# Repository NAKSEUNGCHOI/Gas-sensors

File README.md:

# Project Gas(Air quality) sensors

* University of Washington Summer 2022 
* Prof. Vikram Iyer.
* Nakseung Choi | graduate research assistant @ SSOL UW 

## Description

* Prof. Vikram Iyer and I are currently building low power low cost gas sensors (CO2, CO, and black carbon) to help two groups of scientists collect data for their research studies. One group wants to get data in the greater Seattle area to study on where these gasses are coming from. Ultimately, they would like to expand the number of the gas sensors in different locations such that they can compare with other locations for further studies.
The other group would like to place these gas sensors in the middle of moutains in the eastern Washington to study how these gases(CO2 and CO) affect wild animals when there is an unexpected wildfire going. 

* We are currently testing several CO2 sensors to compare their functionality with a commercial device. In the mean time, we just got done with our own PCB design for SPEC CO sensor as well as hardware/software integration. Depending on how precise data the scientists need, we are going to make it acordingly. nRF52480 Arm Cortex-m4 is probably going to be used for the MCU. Using Lora radio communication, a long distance communication interface will also be implemented to update data to the web server such that the scientists can check the data in real time.  

## Authors

- Nakseung Choi
- Please check out my Linkedin: https://www.linkedin.com/in/nakseung-choi-090a1b69/

## Release Notes

* <pre> New Tube arrived. About to go install the MA350 on the rooftop                       11-22-2022</pre>
* <pre> 300ml/min 60 ml/min for 5 wavelengths tests are done. missing 60 ml/min with UV+IR    9-12-2022</pre>
* <pre> Created another python code to draw different plots for CO2 sensors                   9-12-2022</pre>
* <pre> Wrote a python code to plot CO2 sensors - avg of two aranets for 4 sensors            9-08-2022</pre>
* <pre> wrote a python program using mathplot to graph the CO2 data  (Still testing MA350)    9-07-2022</pre>
* <pre> Testing the MA350                                                                     8-29-2022</pre>
* <pre> arduino / python serial communication script complete. Sending data to adafruitIO     8-26-2022</pre>
* <pre> presentation done. more CO testing / preparing to set up MA350.                       8-24-2022</pre>                                                
* <pre> got the CO sensor working with noise. more testing...........                         8-23-2022</pre>
* <pre> created a new PCB board and testing..                                                 8-22-2022</pre>
* <pre> presentation preparation2                                                             8-20-2022</pre>
* <pre> presentation preparation                                                              8-20-2022</pre>
* <pre> Software done. software/hardware integration started                                  8-18-2022</pre>
* <pre> Testing CO sensor 2                                                                   8-17-2022</pre>
* <pre> Testing CO sensor                                                                     8-16-2022</pre>
* <pre> setting up Black Carbon sensor & CO sensor                                            8-15-2022</pre>
* <pre> testing two SCD41s, two aranets, two PASCO2s all together.                            8-15-2022</pre>
* <pre>Debugging Complete. Ready to go for a testing.                                         8-14-2022</pre>
* <pre>Debugging...                                                                           8-12-2022</pre>
* <pre>PASCO2s are going to be tested with scd41 and aranet4 together for the functionality   8-11-2022</pre>
* <pre>Xensiv PAS CO2 coding in python complete.                                              8-11-2022</pre>
* <pre>Xensiv PAS CO2 working. Testing started.                                               8-10-2022</pre>
* <pre>Debugging Xensiv PAS CO2                                                               8-09-2022</pre>
* <pre>Testing Xensiv PAS CO2 manufactured by Infineon.                                       8-08-2022</pre>
* <pre>All parts are done soldering onto the board. Going to test the PCB.                    8-07-2022</pre>
* <pre>CO sensor PCB design complete. About to sorder the CO sensor circuit.                  8-03-2022</pre> 
* <pre>Designing a new circuit for CO sensor due to the chip shortage (LMP9100 out of stock)  8-02-2022</pre>
* <pre>Installed CO2 sensor's in an office with two people.                                   7-28-2022</pre>
* <pre>CO Sensor PCB Design V2 complete.                                                      7-28-2022</pre>
* <pre>CO Sensor PCB Design complete.                                                         7-27-2022</pre>
* <pre>Testing 24 hours success.                                                              7-26-2022</pre>
* <pre>Testing two SCD41s and two aranets4s on Raspberry pi 3.                                7-25-2022</pre>
* <pre>Working on PCB design for CO sensor                                                    7-24-2022</pre>
* <pre>Implemented two SCD41s and two aranet4s on Raspberry pi 3 for a testing.               7-21-2022</pre>
* <pre>Implemented SCD41 on nRF52480 express with Lora Radio (RFM9x)                          7-07-2022</pre>
* <pre>Implemented SCD41 (via I2C) and Aranet4 (via Bluetooth) on Raspberry pi 3 (B type)     7-01-2022</pre>
* <pre>Started                                                                                6/24/2022</pre>

## License

Copyright @ Nakseung Choi.

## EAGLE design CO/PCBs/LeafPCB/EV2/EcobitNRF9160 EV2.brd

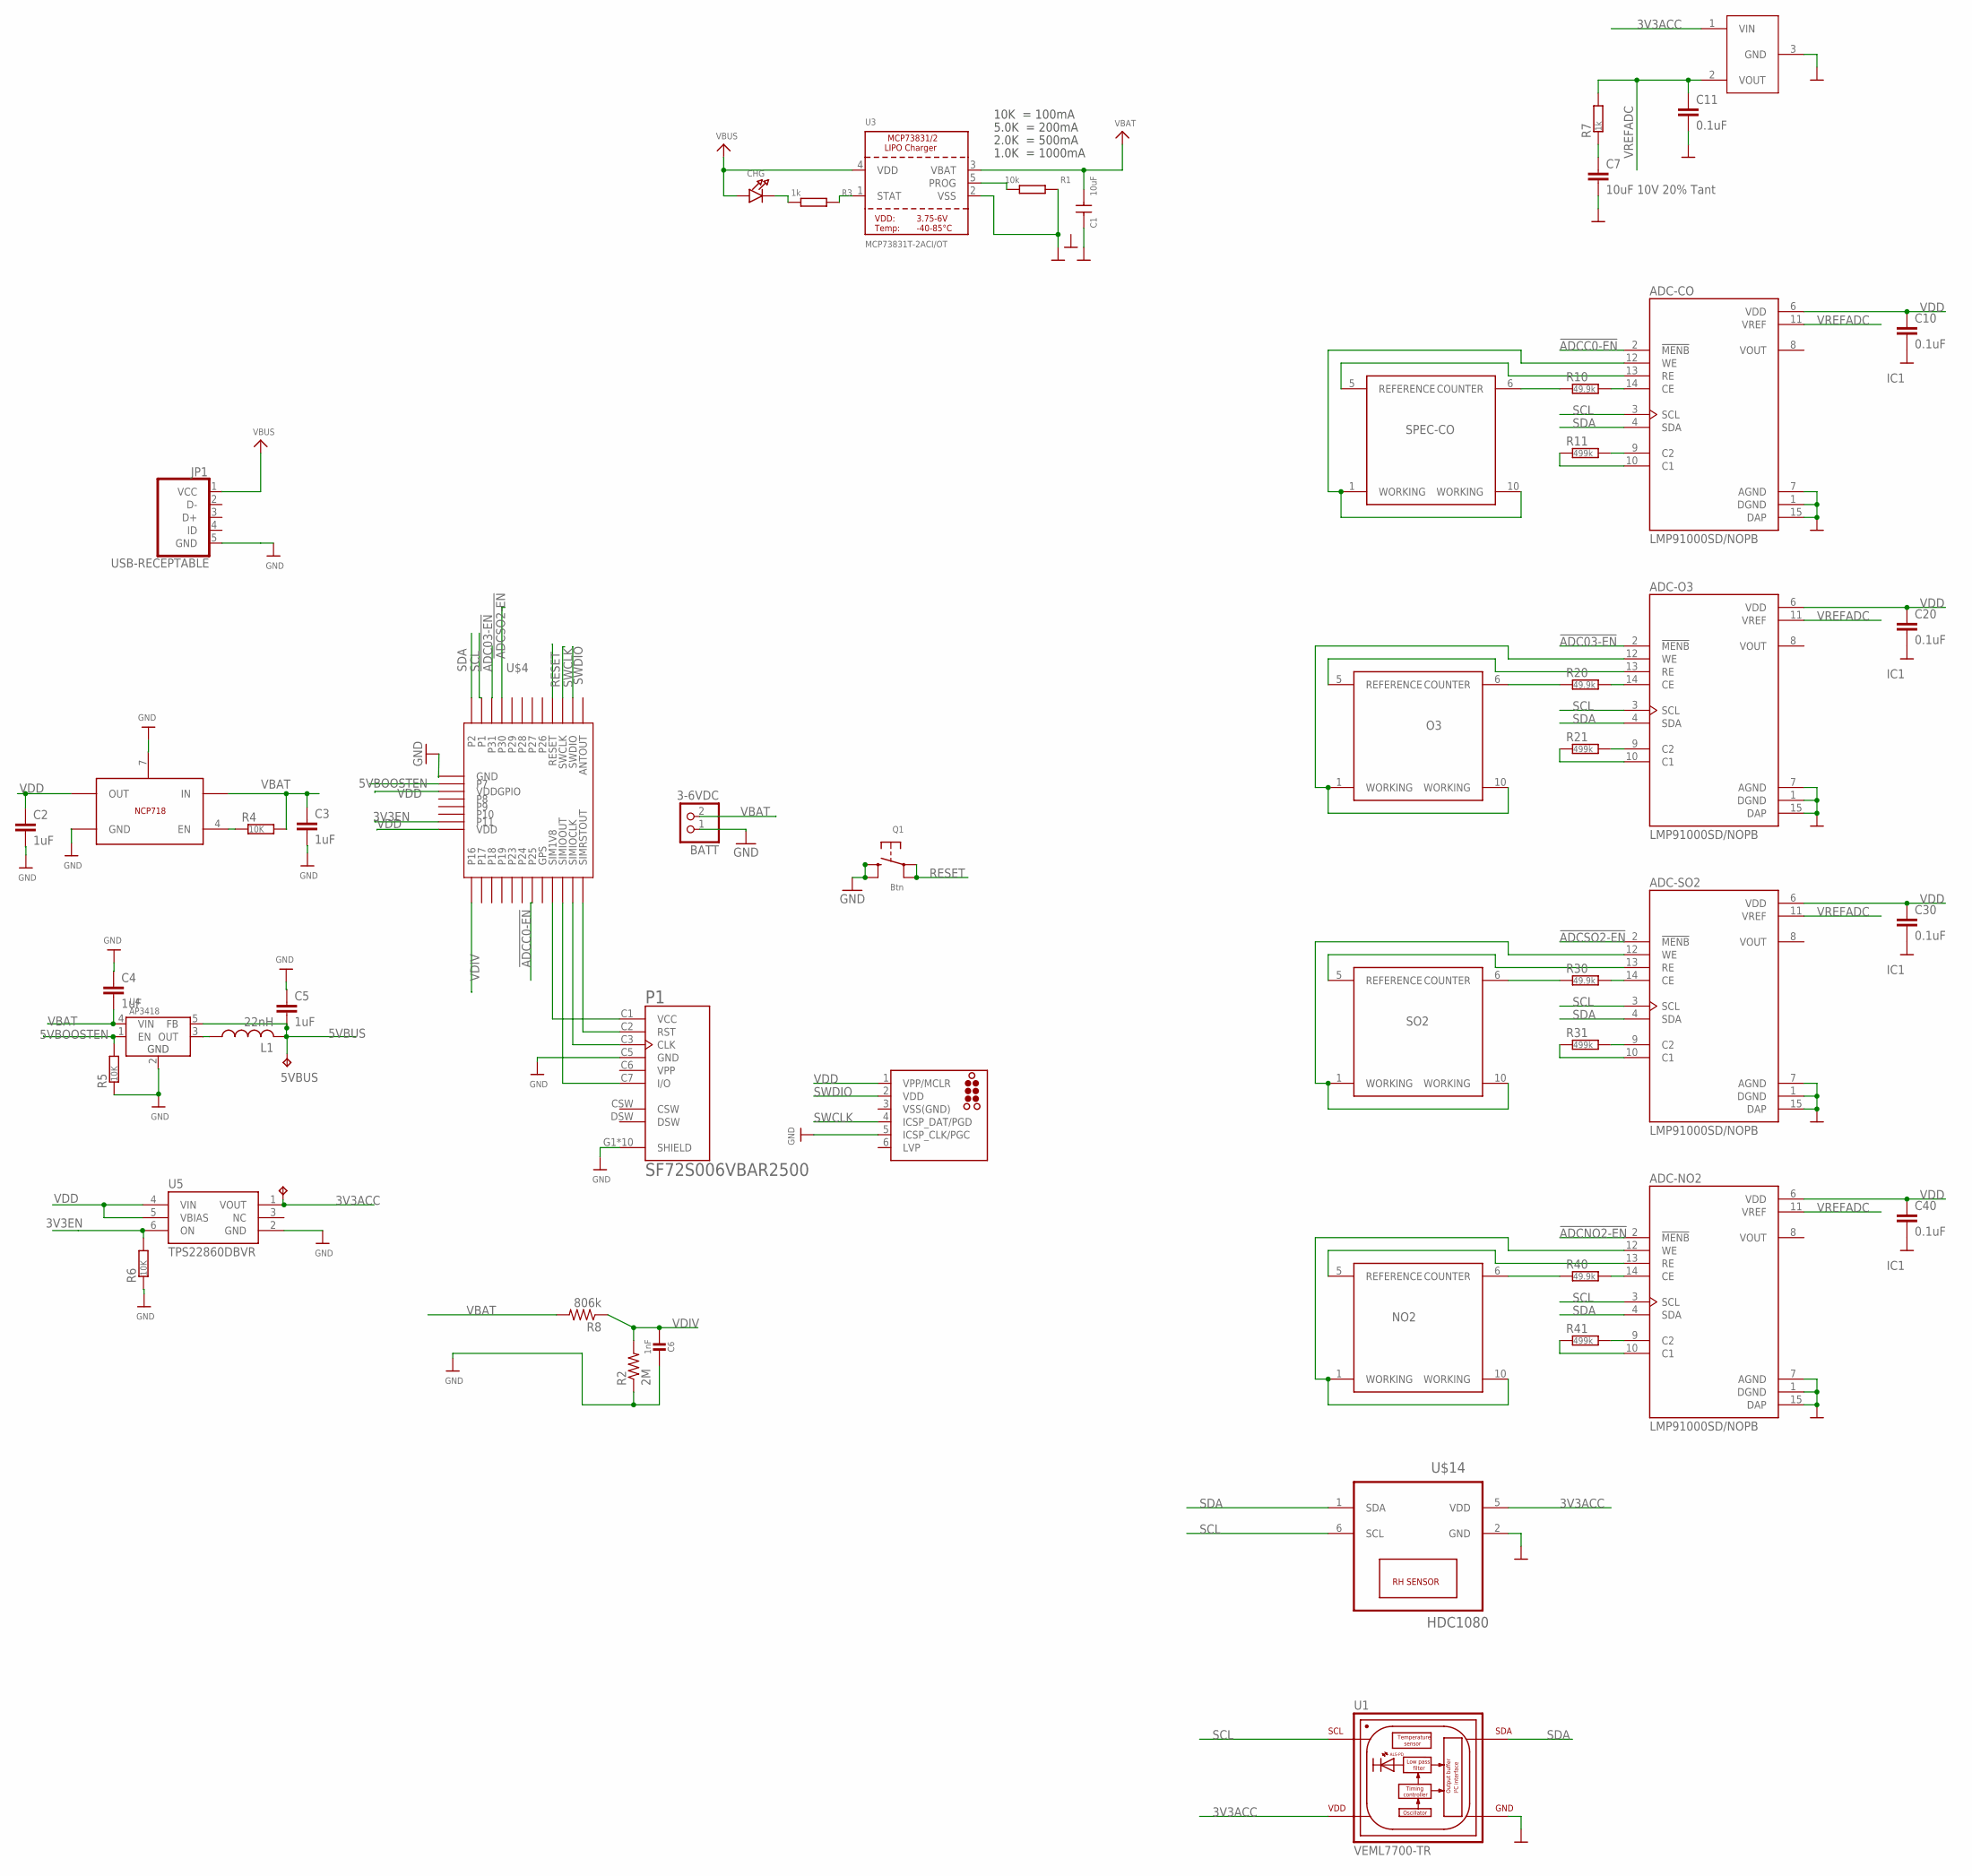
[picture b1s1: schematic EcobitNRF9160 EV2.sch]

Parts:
5VBUS, 5VBUS1: TPTP15R; TP15R
ADC-CO: LMP91000SD/NOPB; SON50P400X400X80-15N
ADC-NO2: LMP91000SD/NOPB; SON50P400X400X80-15N
ADC-O3: LMP91000SD/NOPB; SON50P400X400X80-15N
ADC-SO2: LMP91000SD/NOPB; SON50P400X400X80-15N
BATT: 3-6VDC; JSTPH2
C1: 10uF; C-0402
C2, C3, C4, C5: 1uF; RESC0402_N
C6: 1nF; 0603-NO
C7: 10uF 10V 20% Tant; RESC0805_N
C10, C11, C20, C30, C40: 0.1uF; RESC0603_N
CHG: LED0805_NOOUTLINE; CHIPLED_0805_NOOUTLINE
IC1: ISL60002DIH320Z-TK; SOT-23-3
J2: TC2030-MCP-NL
JP1: USB-RECEPTABLE; FCI-10103594-0001LF
L1: 22nH; RESC0603_N
NO2: SPECSENSOR
O3: SPECSENSOR
P1: SF72S006VBAR2500; JAE_SF72S006VBAR2500
Q1: Btn; BTN_KMR2_4.6X2.8
R1: 10k; R0402
R2: 2M; R0603
R3: 1k; R0402
R4, R5, R6: 10K; RESC0402_N
R7: 1k; RESC0603_N
R8: 806k; R0603
R10, R20, R30, R40: 49.9k; RESC0603_N
R11, R21, R31, R41: 499k; RESC0603_N
SO2: SPECSENSOR
SPEC-CO: SPECSENSOR
U1: VEML7700-TR; XDCR_VEML7700-TR
U2: NCP718; NCP718-WDFN6
U3: MCP73831T-2ACI/OT; SOT23-5
U4: AP3418; SOT25
U5: TPS22860DBVR; R-PDSO-G6
U$4: NRF9160MODULE
U$14: HDC1080; TI-S-PWSON-N6

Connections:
3V3ACC: 5VBUS1.TP, IC1.1 (VIN), U1.2 (VDD), U5.1 (VOUT), U$14.5 (VDD)
3V3EN: R6.2, U5.6 (ON), U$4.P11
5VBOOSTEN: R5.2, U4.1 (EN), U$4.P7
5VBUS: 5VBUS.TP, C5.2, L1.2, U4.5 (FB)
!ADC03-EN: ADC-O3.2 (!MENB), U$4.P31
!ADCC0-EN: ADC-CO.2 (!MENB), U$4.P25
!ADCNO2-EN: ADC-NO2.2 (!MENB)
!ADCSO2-EN: ADC-SO2.2 (!MENB), U$4.P30
GND: ADC-CO.1 (DGND), ADC-CO.7 (AGND), ADC-CO.15 (DAP), ADC-NO2.1 (DGND), ADC-NO2.7 (AGND), ADC-NO2.15 (DAP), ADC-O3.1 (DGND), ADC-O3.7 (AGND), ADC-O3.15 (DAP), ADC-SO2.1 (DGND), ADC-SO2.7 (AGND), ADC-SO2.15 (DAP), BATT.1, C1.2, C2.2, C3.2, C4.1, C5.1, C6.1, C7.2, C10.2, C11.2, C20.2, C30.2, C40.2, IC1.3 (GND), J2.5 (ICSP_CLK/PGC), JP1.5 (GND), P1.C5 (GND), P1.G1 (SHIELD), P1.G2 (SHIELD), P1.G3 (SHIELD), P1.G4 (SHIELD), P1.G5 (SHIELD), P1.G6 (SHIELD), P1.G7 (SHIELD), P1.G8 (SHIELD), P1.G9 (SHIELD), P1.G10 (SHIELD), Q1.B (S), Q1.B' (S1), R1.1, R2.1, R5.1, R6.1, U1.3 (GND), U2.3 (GND), U2.7 (GND), U3.2 (VSS), U4.2 (GND), U5.2 (GND), U$4.GND, U$14.2 (GND)
unnamed: P1.C1 (VCC), U$4.SIM1V8
unnamed: L1.1, U4.3 (OUT)
unnamed: R3.1, U3.1 (STAT)
unnamed: CHG.C, R3.2
unnamed: P1.C2 (RST), U$4.SIMRSTOUT
unnamed: P1.C3 (CLK), U$4.SIMCLKOUT (SIMIOCLK)
unnamed: P1.C7 (I/O), U$4.SIMIOOUT
unnamed: ADC-CO.9 (C2), R11.2
unnamed: ADC-CO.10 (C1), R11.1
unnamed: R1.2, U3.5 (PROG)
unnamed: ADC-CO.14 (CE), R10.2
unnamed: C7.1, R7.1
unnamed: ADC-O3.9 (C2), R21.2
unnamed: ADC-O3.10 (C1), R21.1
unnamed: ADC-O3.14 (CE), R20.2
unnamed: ADC-SO2.9 (C2), R31.2
unnamed: ADC-SO2.10 (C1), R31.1
unnamed: ADC-SO2.14 (CE), R30.2
unnamed: ADC-NO2.9 (C2), R41.2
unnamed: ADC-NO2.10 (C1), R41.1
unnamed: ADC-NO2.14 (CE), R40.2
R-EN: R4.1, U2.4 (EN)
RESET: Q1.A, Q1.A' (P1), U$4.RESET
SCL: ADC-CO.3 (SCL), ADC-NO2.3 (SCL), ADC-O3.3 (SCL), ADC-SO2.3 (SCL), U1.1 (SCL), U$4.P1, U$14.6 (SCL)
SDA: ADC-CO.4 (SDA), ADC-NO2.4 (SDA), ADC-O3.4 (SDA), ADC-SO2.4 (SDA), U1.4 (SDA), U$4.P2, U$14.1 (SDA)
SPEC-CO-COUNTER: R10.1, SPEC-CO.6 (COUNTER)
SPEC-CO-REF: ADC-CO.13 (RE), SPEC-CO.5 (REFERENCE)
SPEC-CO-WKG: ADC-CO.12 (WE), SPEC-CO.1 (WORKING), SPEC-CO.10 (WORKING)
SPEC-NO2-COUNTER: NO2.6 (COUNTER), R40.1
SPEC-NO2-REF: ADC-NO2.13 (RE), NO2.5 (REFERENCE)
SPEC-NO2-WKG: ADC-NO2.12 (WE), NO2.1 (WORKING), NO2.10 (WORKING)
SPEC-O3-COUNTER: O3.6 (COUNTER), R20.1
SPEC-O3-REF: ADC-O3.13 (RE), O3.5 (REFERENCE)
SPEC-O3-WKG: ADC-O3.12 (WE), O3.1 (WORKING), O3.10 (WORKING)
SPEC-SO2-COUNTER: R30.1, SO2.6 (COUNTER)
SPEC-SO2-REF: ADC-SO2.13 (RE), SO2.5 (REFERENCE)
SPEC-SO2-WKG: ADC-SO2.12 (WE), SO2.1 (WORKING), SO2.10 (WORKING)
SWCLK: J2.4 (ICSP_DAT/PGD), U$4.SWCLK
SWDIO: J2.2 (VDD), U$4.SWDIO
VBAT: BATT.2, C1.1, C3.1, C4.2, R4.2, R8.2, U2.6 (IN), U3.3 (VBAT), U4.4 (VIN)
VBUS: CHG.A, JP1.1 (VCC), U3.4 (VDD)
VDD: ADC-CO.6 (VDD), ADC-NO2.6 (VDD), ADC-O3.6 (VDD), ADC-SO2.6 (VDD), C2.1, C10.1, C20.1, C30.1, C40.1, J2.1 (VPP/MCLR), U2.1 (OUT), U5.4 (VIN), U5.5 (VBIAS), U$4.VDD, U$4.VDDGPIO
VDIV: C6.2, R2.2, R8.1, U$4.P16
VPP: P1.C6 (VPP)
VREFADC: ADC-CO.11 (VREF), ADC-NO2.11 (VREF), ADC-O3.11 (VREF), ADC-SO2.11 (VREF), C11.1, IC1.2 (VOUT), R7.2
VSS(GND): J2.3 (VSS(GND))

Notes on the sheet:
10K = 100mA
5.0K = 200mA
2.0K = 500mA
1.0K = 1000mA

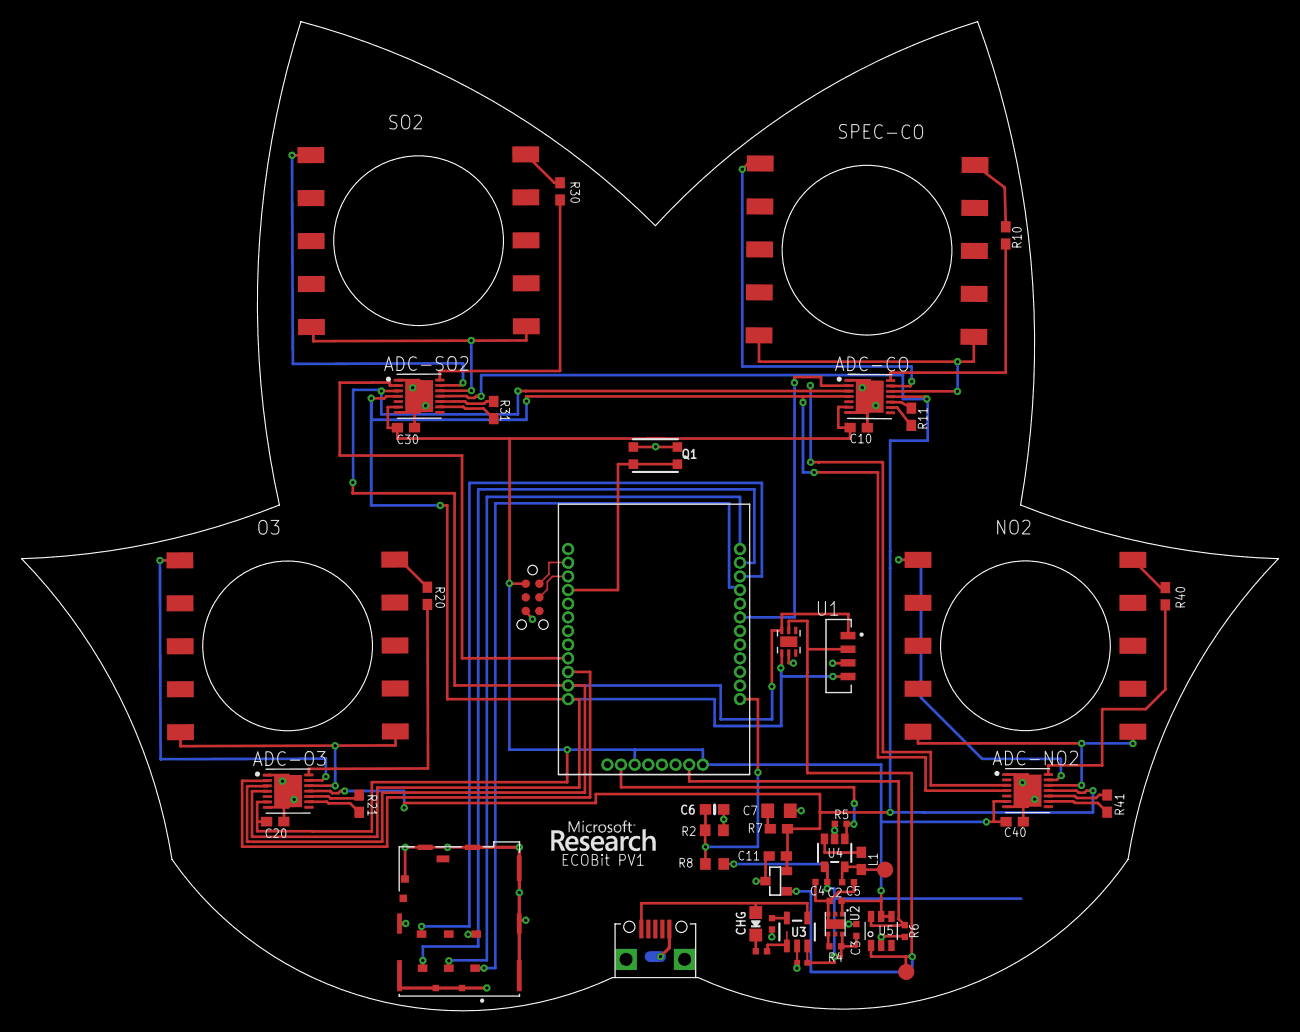
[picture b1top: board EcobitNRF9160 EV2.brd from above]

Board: 2 copper layers, 117.0 x 92.1 mm, 53 parts (1 on the bottom side), 52 nets.

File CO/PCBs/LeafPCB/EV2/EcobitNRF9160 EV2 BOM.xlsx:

Column1 | Column2 | Column3 | Column4
Part | Value | Device | Package
ADC-CO | LMP91000SD/NOPB | LMP91000SD/NOPB | SON50P400X400X80-15N
ADC-NO2 | LMP91000SD/NOPB | LMP91000SD/NOPB | SON50P400X400X80-15N
ADC-O3 | LMP91000SD/NOPB | LMP91000SD/NOPB | SON50P400X400X80-15N
ADC-SO2 | LMP91000SD/NOPB | LMP91000SD/NOPB | SON50P400X400X80-15N
BATT | 3-6VDC | CON_JST_PH_2PIN | JSTPH2
C1 | 10uF | CAP0402 | C-0402
C2, C3, C4, C5, C6 | 1uF | CAPACITOR_0402_N | RESC0402_N
C7 | 10uF 10V 20% Tant | CAPACITOR_0805_N | RESC0805_N
C10, C11, C20, C30, C40 | 0.1uF | CAPACITOR_0603_N | RESC0603_N
CHG |  | LED0805_NOOUTLINE | CHIPLED_0805_NOOUTLINE
IC1 | ISL60002DIH320Z-TK | ISL60002DIH320Z-TK | SOT-23-3
JP1 | USB-RECEPTABLE | USB-RECEPTABLE | FCI-10103594-0001LF
L1 | 22nH | INDUCTOR_0603_N | RESC0603_N
P1 | SF72S006VBAR2500 | SF72S006VBAR2500 | JAE_SF72S006VBAR2500
Q1 | Btn | SWITCH_TACT_SMT4.6X2.8 | BTN_KMR2_4.6X2.8
R1, R4, R5, R6 | 10k | RESR0402 | R0402
R2 | 2M | R-US_R0603 | R0603
R3, R7 | 1k | RESR0402 | R0402
R11, R21, R31, R41 | 499k | RESISTOR_0603_N | RESC0603_N
R8 | 806k | R-US_R0603 | R0603
R10, R20, R30, R40 | 49.9k | RESISTOR_0603_N | RESC0603_N
IC2 | HDC1080 | HDC1080 | TI-S-PWSON-N6
U1 | VEML7700-TR | VEML7700-TR | XDCR_VEML7700-TR
U2 | NCP718 | NCP718 | NCP718-WDFN6
U3 | MCP73831T-2ACI/OT | MCP73831/2 | SOT23-5
U4 | AP3418 | AP3418 | SOT25
U5 | TPS22860DBVR | TPS22860DBVR | R-PDSO-G6
U6 | MCP6041T-I/OT

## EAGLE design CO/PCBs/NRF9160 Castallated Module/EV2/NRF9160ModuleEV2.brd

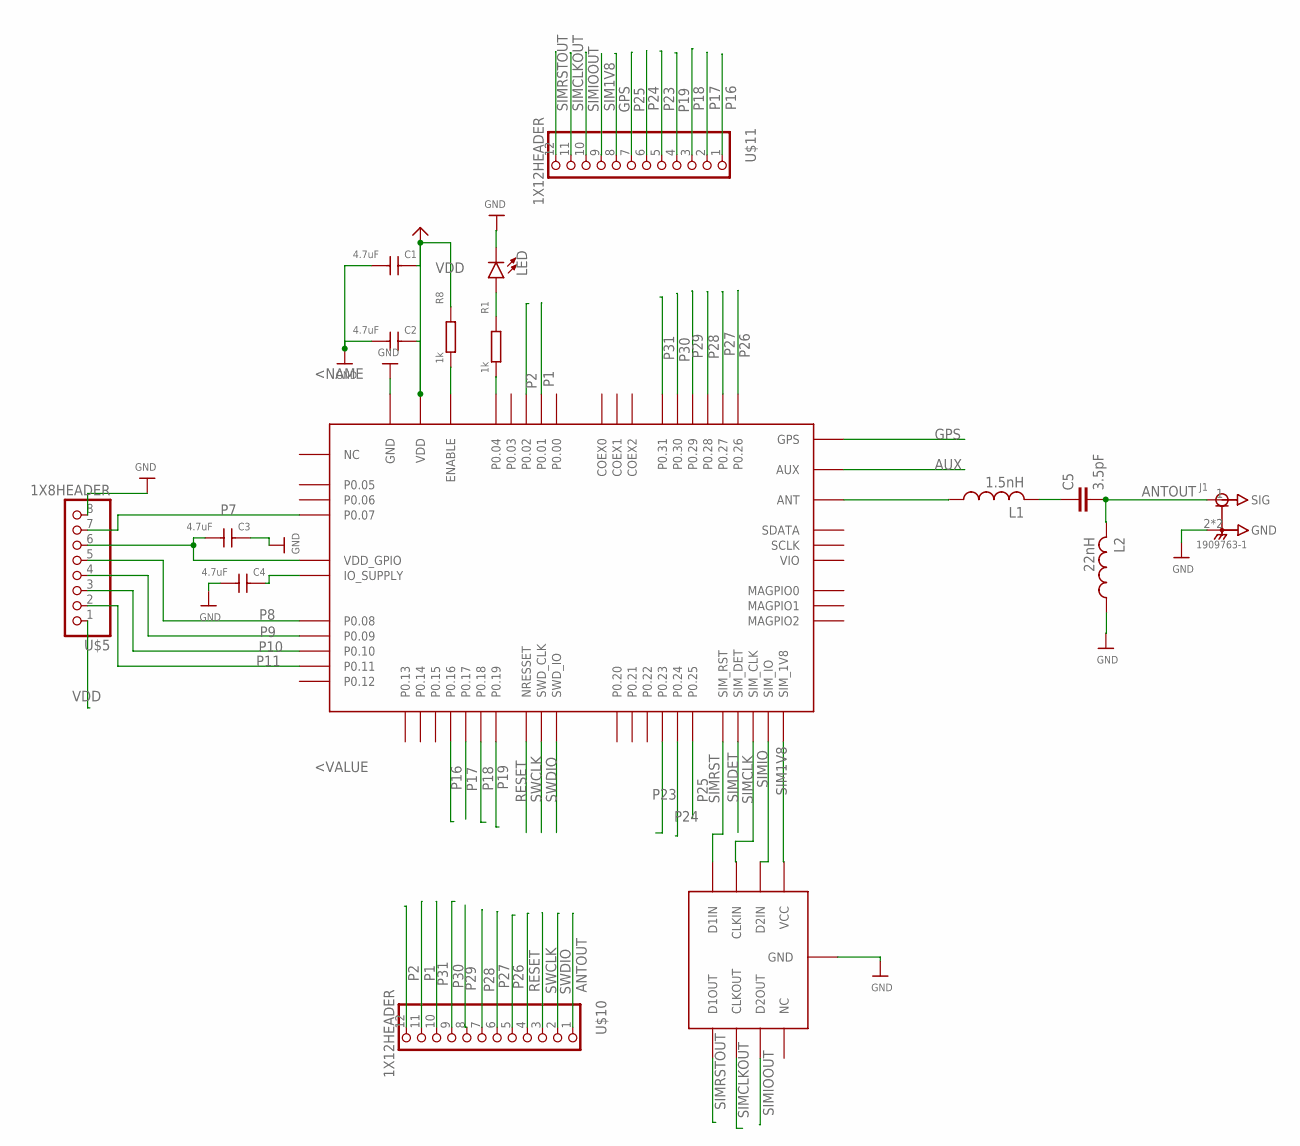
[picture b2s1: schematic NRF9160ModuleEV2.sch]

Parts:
C1, C2, C3, C4: 4.7uF; C-0402
C5: 3.5pF; RESC0402_N
IC1: NRF9160
J1: 1909763-1; TE_1909763-1
L1: 1.5nH; RESC0603_N
L2: 22nH; RESC0603_N
LED: LED0603; LED-0603
R1, R8: 1k; R0402
U1: TPD3F303; 8-UFDFN
U$5: 1X8HEADER; 8X1
U$10, U$11: 1X12HEADER; 1X12

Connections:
ANTOUT: C5.2, J1.1 (SIG), L2.2, U$10.1
AUX: IC1.AUX
GND: C1.1, C2.1, C3.2, C4.1, IC1.GND@1 (GND), IC1.GND@2 (GND), IC1.GND@3 (GND), IC1.GND@4 (GND), IC1.GND@5 (GND), IC1.GND@6 (GND), IC1.GND@7 (GND), IC1.GND@8 (GND), IC1.GND@9 (GND), IC1.GND@10 (GND), IC1.GND@11 (GND), IC1.GND@12 (GND), IC1.GND@13 (GND), IC1.GND@14 (GND), IC1.GND@15 (GND), IC1.GND@16 (GND), IC1.GND@17 (GND), IC1.GND@18 (GND), IC1.GND@19 (GND), IC1.GND@20 (GND), IC1.GND@21 (GND), IC1.GND@22 (GND), IC1.GND@23 (GND), IC1.GND@24 (GND), IC1.GND@25 (GND), IC1.GND@26 (GND), IC1.GND@27 (GND), IC1.GND@28 (GND), IC1.GND@29 (GND), IC1.GND@30 (GND), IC1.GND@31 (GND), IC1.GND@32 (GND), IC1.GND@33 (GND), IC1.GND@34 (GND), IC1.GND@35 (GND), IC1.GND_SHIELD@1 (GND), IC1.GND_SHIELD@2 (GND), IC1.GND_SHIELD@3 (GND), IC1.GND_SHIELD@4 (GND), IC1.GND_SHIELD@5 (GND), IC1.GND_SHIELD@6 (GND), IC1.GND_SHIELD@7 (GND), IC1.GND_SHIELD@8 (GND), IC1.GND_SHIELD@9 (GND), IC1.GND_SHIELD@10 (GND), IC1.GND_SHIELD@11 (GND), IC1.GND_SHIELD@12 (GND), IC1.GND_SHIELD@13 (GND), IC1.GND_SHIELD@14 (GND), IC1.GND_SHIELD@15 (GND), IC1.GND_SHIELD@16 (GND), IC1.GND_SHIELD@17 (GND), IC1.GND_SHIELD@18 (GND), IC1.GND_SHIELD@19 (GND), IC1.GND_SHIELD@20 (GND), IC1.GND_SHIELD@21 (GND), IC1.GND_SHIELD@22 (GND), IC1.GND_SHIELD@23 (GND), IC1.GND_SHIELD@24 (GND), IC1.GND_SHIELD@25 (GND), IC1.GND_SHIELD@26 (GND), IC1.GND_SHIELD@27 (GND), IC1.GND_SHIELD@28 (GND), IC1.GND_SHIELD@29 (GND), IC1.GND_SHIELD@30 (GND), IC1.GND_SHIELD@31 (GND), IC1.GND_SHIELD@32 (GND), IC1.GND_SHIELD@33 (GND), IC1.GND_SHIELD@34 (GND), J1.2 (GND), J1.3 (GND), L2.1, LED.C, U1.P$9 (GND), U$5.8
GPS: IC1.GPS, U$11.8
unnamed: IC1.ENABLE, R8.2
unnamed: C4.2, IC1.IO_SUPPLY
unnamed: C3.1, IC1.VDD_GPIO, U$5.6
unnamed: IC1.P0.04, R1.2
unnamed: LED.A, R1.1
unnamed: IC1.ANT, L1.1
unnamed: C5.1, L1.2
P1: IC1.P0.01, U$10.11
P2: IC1.P0.02, U$10.12
P7: IC1.P0.07, U$5.7
P8: IC1.P0.08, U$5.5
P9: IC1.P0.09, U$5.4
P10: IC1.P0.10, U$5.3
P11: IC1.P0.11, U$5.2
P16: IC1.P0.16, U$11.1
P17: IC1.P0.17, U$11.2
P18: IC1.P0.18, U$11.3
P19: IC1.P0.19, U$11.4
P23: IC1.P0.23, U$11.5
P24: IC1.P0.24, U$11.6
P25: IC1.P0.25, U$11.7
P26: IC1.P0.26, U$10.5
P27: IC1.P0.27, U$10.6
P28: IC1.P0.28, U$10.7
P29: IC1.P0.29, U$10.8
P30: IC1.P0.30, U$10.9
P31: IC1.P0.31, U$10.10
RESET: IC1.NRESET (NRESSET), U$10.4
SIM1V8: IC1.SIM_1V8, U1.VCC, U$11.9
SIMCLK: IC1.SIM_CLK, U1.CLKIN
SIMCLKOUT: U1.CLKOUT, U$11.11
SIMDET: IC1.SIM_DET
SIMIO: IC1.SIM_IO, U1.D2IN
SIMIOOUT: U1.D2OUT, U$11.10
SIMRST: IC1.SIM_RST, U1.D1IN
SIMRSTOUT: U1.D1OUT, U$11.12
SWCLK: IC1.SWDCLK (SWD_CLK), U$10.3
SWDIO: IC1.SWDIO (SWD_IO), U$10.2
VDD: C1.2, C2.2, IC1.VDD@1 (VDD), IC1.VDD@2 (VDD), R8.1, U$5.1

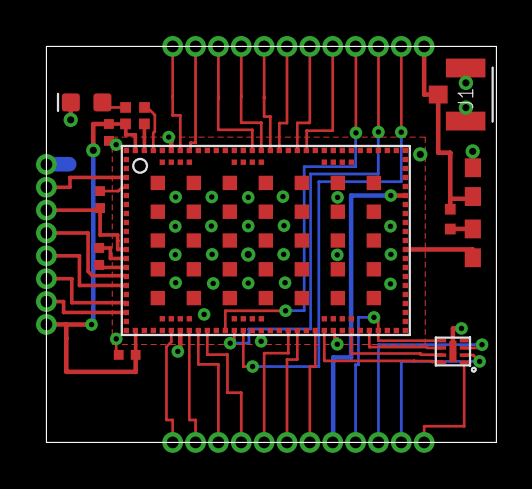
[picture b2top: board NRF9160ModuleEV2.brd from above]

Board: 2 copper layers, 25.0 x 22.0 mm, 16 parts (0 on the bottom side), 41 nets.

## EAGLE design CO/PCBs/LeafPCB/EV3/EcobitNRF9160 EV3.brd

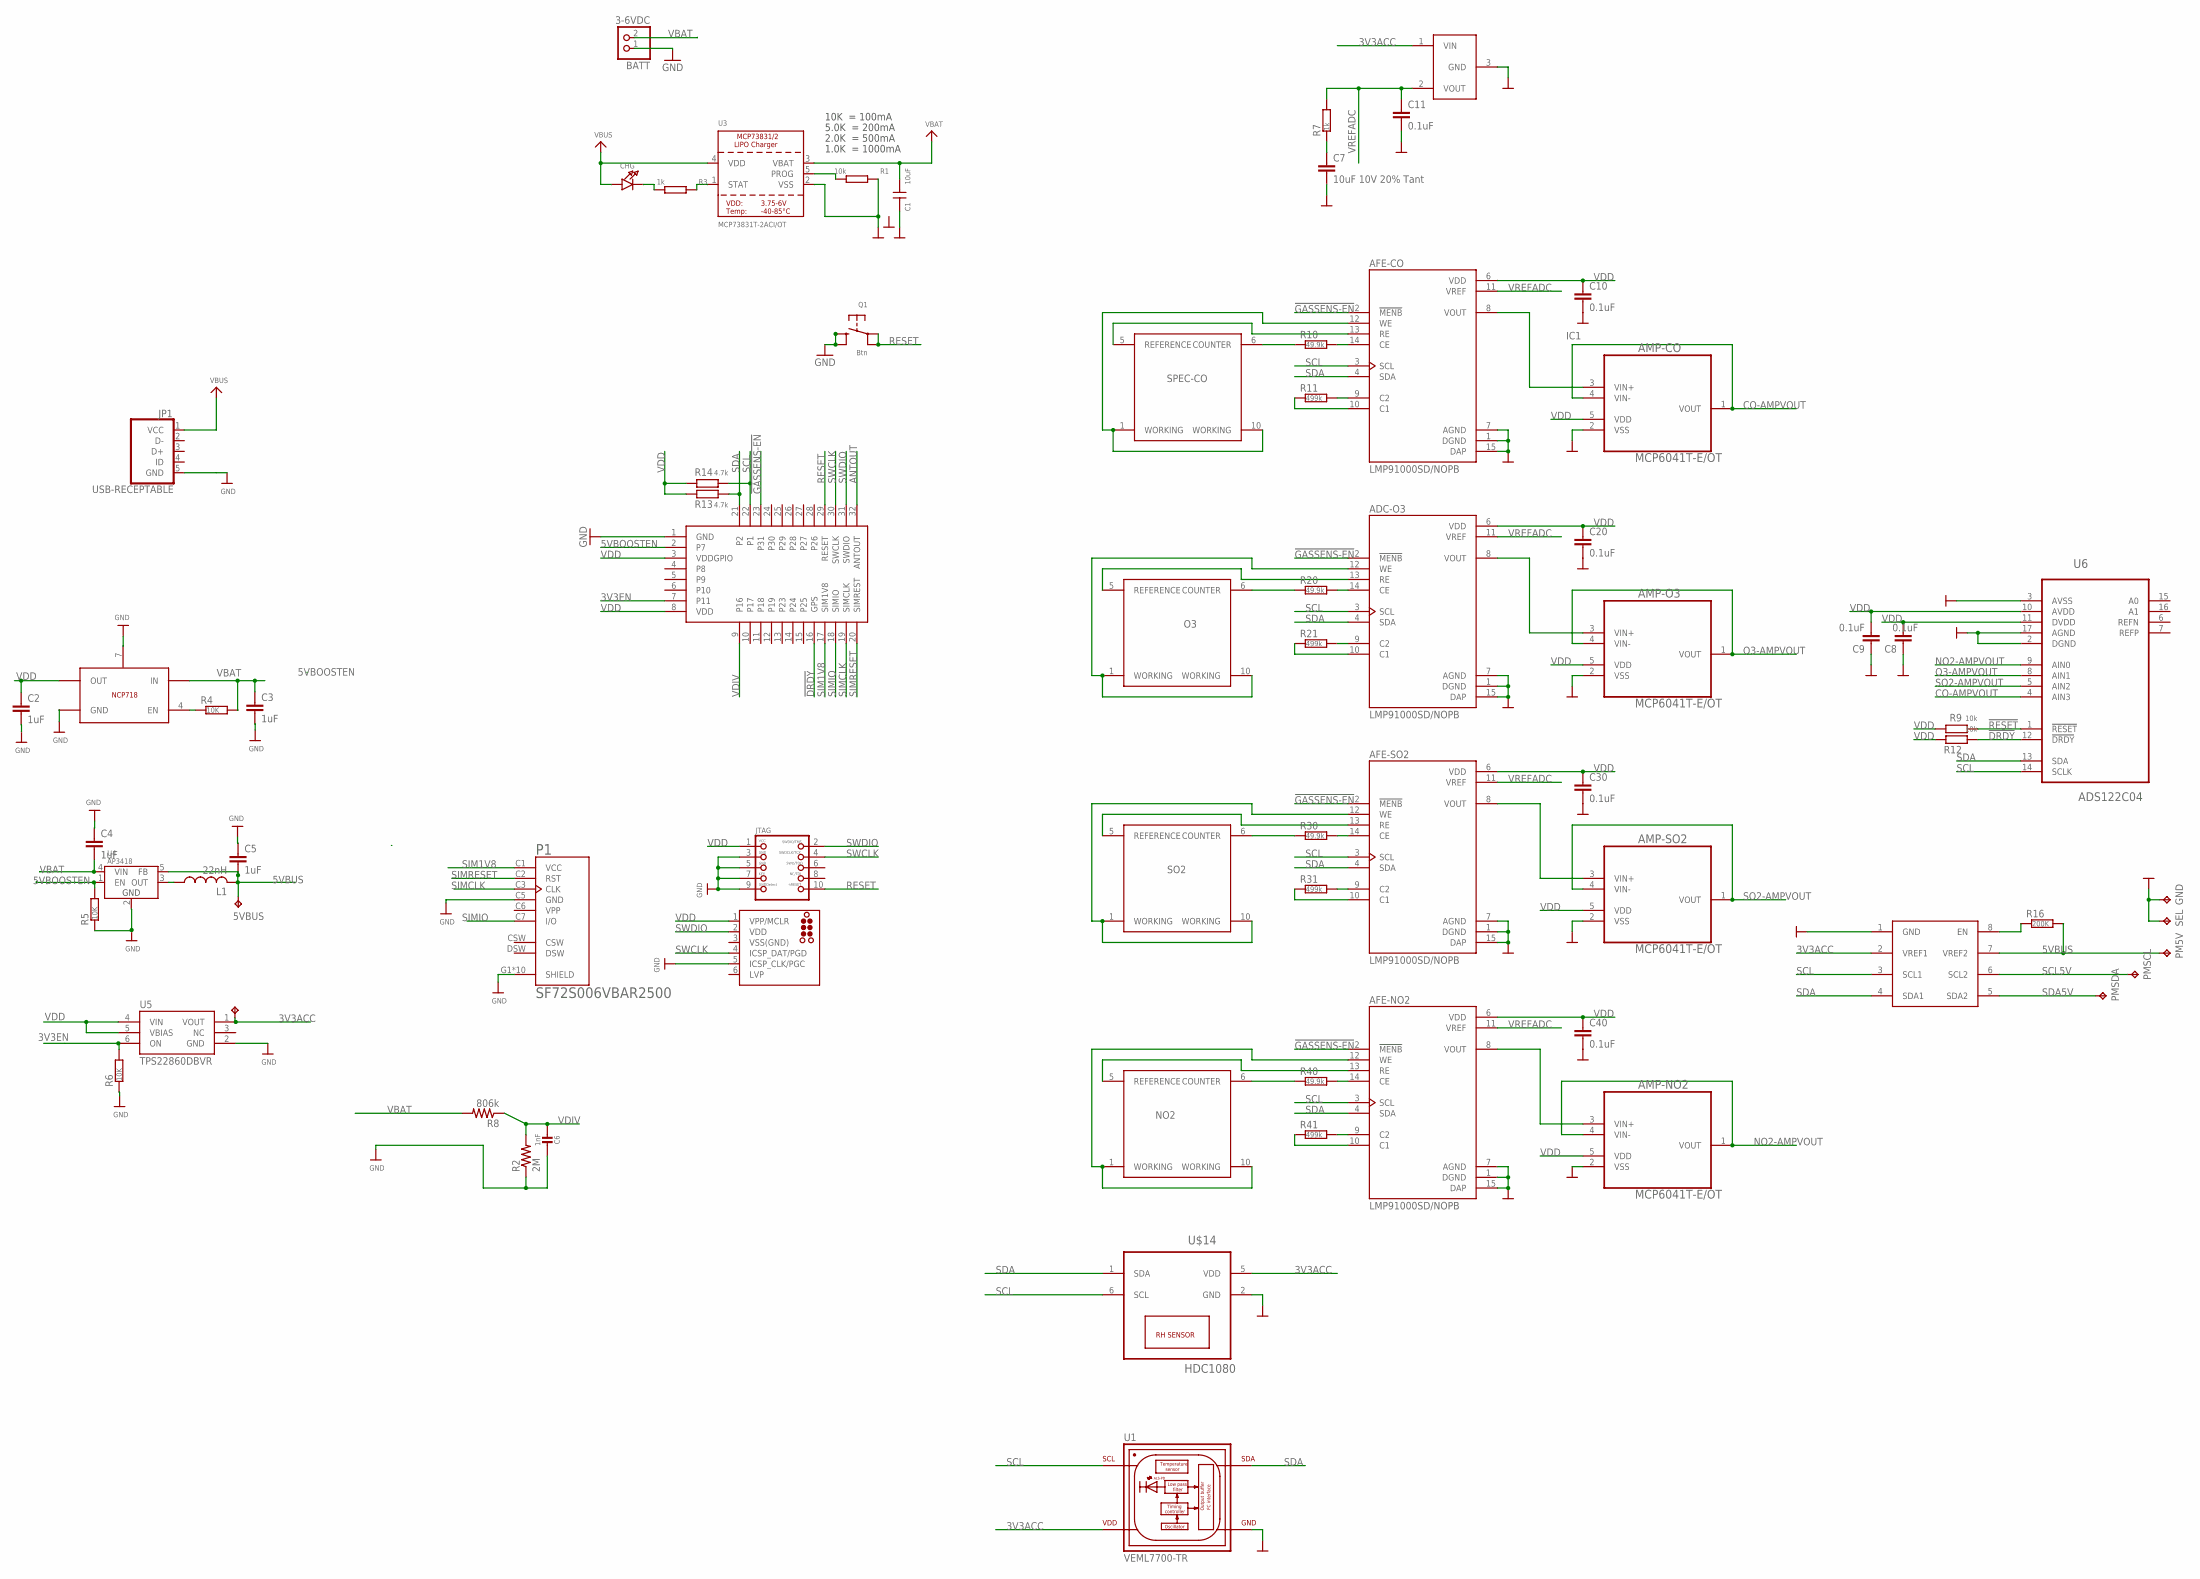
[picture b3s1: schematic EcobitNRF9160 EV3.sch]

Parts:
5VBUS, 5VBUS1: TPTP15R; TP15R
ADC-O3: LMP91000SD/NOPB; SON50P400X400X80-15N
AFE-CO: LMP91000SD/NOPB; SON50P400X400X80-15N
AFE-NO2: LMP91000SD/NOPB; SON50P400X400X80-15N
AFE-SO2: LMP91000SD/NOPB; SON50P400X400X80-15N
AMP-CO: MCP6041T-E/OT; SOT95P320X145-5N
AMP-NO2: MCP6041T-E/OT; SOT95P320X145-5N
AMP-O3: MCP6041T-E/OT; SOT95P320X145-5N
AMP-SO2: MCP6041T-E/OT; SOT95P320X145-5N
BATT: 3-6VDC; JSTPH2
C1: 10uF; C-0402
C2, C3, C4, C5: 1uF; RESC0402_N
C6: 1nF; 0603-NO
C7: 10uF 10V 20% Tant; RESC0805_N
C8, C9, C10, C11, C20, C30, C40: 0.1uF; RESC0603_N
CHG: LED0805_NOOUTLINE; CHIPLED_0805_NOOUTLINE
GND: TPTP15R; TP15R
IC1: ISL60002DIH320Z-TK; SOT-23-3
J2: TC2030-MCP-NL
JP1: USB-RECEPTABLE; FCI-10103594-0001LF
JTAG: JTAG-CORTEXM3; 2X05_1.27MM_SMT
L1: 22nH; RESC0603_N
P1: SF72S006VBAR2500; JAE_SF72S006VBAR2500
PM5V: TPTP15R; TP15R
PMSCL: TPTP15R; TP15R
PMSDA: TPTP15R; TP15R
Q1: Btn; BTN_KMR2_4.6X2.8
R1: 10k; R0402
R2: 2M; R0603
R3: 1k; R0402
R4, R5, R6: 10K; RESC0402_N
R7: 1k; RESC0603_N
R8: 806k; R0603
R9, R12: 10k; RESC0603_N
R10, R20, R30, R40: 49.9k; RESC0603_N
R11, R21, R31, R41: 499k; RESC0603_N
R13, R14: 4.7k; RESC0603_N
R16: 200K; RESC0402_N
SEL: TPTP15R; TP15R
SENS-CO: SPECSENSOR
SENS-NO2: SPECSENSOR
SENS-O3: SPECSENSOR
SENS-SO2: SPECSENSOR
U1: VEML7700-TR; XDCR_VEML7700-TR
U2: NCP718; NCP718-WDFN6
U3: MCP73831T-2ACI/OT; SOT23-5
U4: AP3418; SOT25
U5: TPS22860DBVR; R-PDSO-G6
U6: ADS122C04; QFN50P300X300X80-16N
U7: PCA9306; PSON35P135X100X50-8N
U$14: HDC1080; TI-S-PWSON-N6
U$35: NRF9160MODULE; NRF9160CASTALLATEDMODULE

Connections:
3V3ACC: 5VBUS1.TP, IC1.1 (VIN), U1.2 (VDD), U5.1 (VOUT), U7.2 (VREF1), U$14.5 (VDD)
3V3EN: R6.2, U5.6 (ON), U$35.7 (P11)
5VBOOSTEN: R5.2, U4.1 (EN), U$35.2 (P7)
5VBUS: 5VBUS.TP, C5.2, L1.2, PM5V.TP, R16.2, U4.5 (FB), U7.7 (VREF2)
!DRDY: R12.1, U6.12 (!DRDY), U$35.16 (GPS)
!GASSENS-EN: ADC-O3.2 (!MENB), AFE-CO.2 (!MENB), AFE-NO2.2 (!MENB), AFE-SO2.2 (!MENB), U$35.23 (P31)
!RESET: R9.1, U6.1 (!RESET)
ANTOUT: U$35.32 (ANTOUT)
CO-AMPVOUT: AMP-CO.1 (VOUT), AMP-CO.4 (VIN-), U6.4 (AIN3)
COVOUT: AFE-CO.8 (VOUT), AMP-CO.3 (VIN+)
GND: ADC-O3.1 (DGND), ADC-O3.7 (AGND), ADC-O3.15 (DAP), AFE-CO.1 (DGND), AFE-CO.7 (AGND), AFE-CO.15 (DAP), AFE-NO2.1 (DGND), AFE-NO2.7 (AGND), AFE-NO2.15 (DAP), AFE-SO2.1 (DGND), AFE-SO2.7 (AGND), AFE-SO2.15 (DAP), AMP-CO.2 (VSS), AMP-NO2.2 (VSS), AMP-O3.2 (VSS), AMP-SO2.2 (VSS), BATT.1, C1.2, C2.2, C3.2, C4.1, C5.1, C6.1, C7.2, C8.1, C9.1, C10.2, C11.2, C20.2, C30.2, C40.2, GND.TP, IC1.3 (GND), J2.5 (ICSP_CLK/PGC), JP1.5 (GND), JTAG.3, JTAG.5, JTAG.7, JTAG.9, P1.C5 (GND), P1.G1 (SHIELD), P1.G2 (SHIELD), P1.G3 (SHIELD), P1.G4 (SHIELD), P1.G5 (SHIELD), P1.G6 (SHIELD), P1.G7 (SHIELD), P1.G8 (SHIELD), P1.G9 (SHIELD), P1.G10 (SHIELD), Q1.B (S), Q1.B' (S1), R1.1, R2.1, R5.1, R6.1, SEL.TP, U1.3 (GND), U2.3 (GND), U2.7 (GND), U3.2 (VSS), U4.2 (GND), U5.2 (GND), U6.2 (DGND), U6.3 (AVSS), U6.17 (AGND), U7.1 (GND), U$14.2 (GND), U$35.1 (GND)
unnamed: R16.1, U7.8 (EN)
unnamed: L1.1, U4.3 (OUT)
unnamed: R3.1, U3.1 (STAT)
unnamed: CHG.C, R3.2
unnamed: AFE-CO.9 (C2), R11.2
unnamed: AFE-CO.10 (C1), R11.1
unnamed: R1.2, U3.5 (PROG)
unnamed: AFE-CO.14 (CE), R10.2
unnamed: C7.1, R7.1
unnamed: ADC-O3.9 (C2), R21.2
unnamed: ADC-O3.10 (C1), R21.1
unnamed: ADC-O3.14 (CE), R20.2
unnamed: AFE-SO2.9 (C2), R31.2
unnamed: AFE-SO2.10 (C1), R31.1
unnamed: AFE-SO2.14 (CE), R30.2
unnamed: AFE-NO2.9 (C2), R41.2
unnamed: AFE-NO2.10 (C1), R41.1
unnamed: AFE-NO2.14 (CE), R40.2
NO2-AMPVOUT: AMP-NO2.1 (VOUT), AMP-NO2.4 (VIN-), U6.9 (AIN0)
NO2VOUT: AFE-NO2.8 (VOUT), AMP-NO2.3 (VIN+)
O3-AMPVOUT: AMP-O3.1 (VOUT), AMP-O3.4 (VIN-), U6.8 (AIN1)
O3VOUT: ADC-O3.8 (VOUT), AMP-O3.3 (VIN+)
R-EN: R4.1, U2.4 (EN)
RESET: JTAG.10, Q1.A, Q1.A' (P1), U$35.29 (RESET)
SCL: ADC-O3.3 (SCL), AFE-CO.3 (SCL), AFE-NO2.3 (SCL), AFE-SO2.3 (SCL), R14.1, U1.1 (SCL), U6.14 (SCLK), U7.3 (SCL1), U$14.6 (SCL), U$35.22 (P1)
SCL5V: PMSCL.TP, U7.6 (SCL2)
SDA: ADC-O3.4 (SDA), AFE-CO.4 (SDA), AFE-NO2.4 (SDA), AFE-SO2.4 (SDA), R13.1, U1.4 (SDA), U6.13 (SDA), U7.4 (SDA1), U$14.1 (SDA), U$35.21 (P2)
SDA5V: PMSDA.TP, U7.5 (SDA2)
SIM1V8: P1.C1 (VCC), U$35.17 (SIM1V8)
SIMCLK: P1.C3 (CLK), U$35.19 (SIMCLK)
SIMIO: P1.C7 (I/O), U$35.18 (SIMIO)
SIMRESET: P1.C2 (RST), U$35.20 (SIMREST)
SO2-AMPVOUT: AMP-SO2.1 (VOUT), AMP-SO2.4 (VIN-), U6.5 (AIN2)
SO2VOUT: AFE-SO2.8 (VOUT), AMP-SO2.3 (VIN+)
SPEC-CO-COUNTER: R10.1, SENS-CO.6 (COUNTER)
SPEC-CO-REF: AFE-CO.13 (RE), SENS-CO.5 (REFERENCE)
SPEC-CO-WKG: AFE-CO.12 (WE), SENS-CO.1 (WORKING), SENS-CO.10 (WORKING)
SPEC-NO2-COUNTER: R40.1, SENS-NO2.6 (COUNTER)
SPEC-NO2-REF: AFE-NO2.13 (RE), SENS-NO2.5 (REFERENCE)
SPEC-NO2-WKG: AFE-NO2.12 (WE), SENS-NO2.1 (WORKING), SENS-NO2.10 (WORKING)
SPEC-O3-COUNTER: R20.1, SENS-O3.6 (COUNTER)
SPEC-O3-REF: ADC-O3.13 (RE), SENS-O3.5 (REFERENCE)
SPEC-O3-WKG: ADC-O3.12 (WE), SENS-O3.1 (WORKING), SENS-O3.10 (WORKING)
SPEC-SO2-COUNTER: R30.1, SENS-SO2.6 (COUNTER)
SPEC-SO2-REF: AFE-SO2.13 (RE), SENS-SO2.5 (REFERENCE)
SPEC-SO2-WKG: AFE-SO2.12 (WE), SENS-SO2.1 (WORKING), SENS-SO2.10 (WORKING)
SWCLK: J2.4 (ICSP_DAT/PGD), JTAG.4, U$35.30 (SWCLK)
SWDIO: J2.2 (VDD), JTAG.2, U$35.31 (SWDIO)
VBAT: BATT.2, C1.1, C3.1, C4.2, R4.2, R8.2, U2.6 (IN), U3.3 (VBAT), U4.4 (VIN)
VBUS: CHG.A, JP1.1 (VCC), U3.4 (VDD)
VDD: ADC-O3.6 (VDD), AFE-CO.6 (VDD), AFE-NO2.6 (VDD), AFE-SO2.6 (VDD), AMP-CO.5 (VDD), AMP-NO2.5 (VDD), AMP-O3.5 (VDD), AMP-SO2.5 (VDD), C2.1, C8.2, C9.2, C10.1, C20.1, C30.1, C40.1, J2.1 (VPP/MCLR), JTAG.1, R9.2, R12.2, R13.2, R14.2, U2.1 (OUT), U5.4 (VIN), U5.5 (VBIAS), U6.10 (AVDD), U6.11 (DVDD), U$35.3 (VDDGPIO), U$35.8 (VDD)
VDIV: C6.2, R2.2, R8.1, U$35.9 (P16)
VPP: P1.C6 (VPP)
VREFADC: ADC-O3.11 (VREF), AFE-CO.11 (VREF), AFE-NO2.11 (VREF), AFE-SO2.11 (VREF), C11.1, IC1.2 (VOUT), R7.2
VSS(GND): J2.3 (VSS(GND))

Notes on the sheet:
10K = 100mA
5.0K = 200mA
2.0K = 500mA
1.0K = 1000mA

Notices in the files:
parts and their libraries:
SparkFun-LED: Licensing: Creative Commons ShareAlike 4.0 International - https://creativecommons.org/licenses/by-sa/4.0
microbuilder: This work is placed in the public domain, and may be freely used for commercial and non-commercial work with the following conditions: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
